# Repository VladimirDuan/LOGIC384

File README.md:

# LOGIC384
384LUTs ARM Cortex-M3&amp;FPGA development board.

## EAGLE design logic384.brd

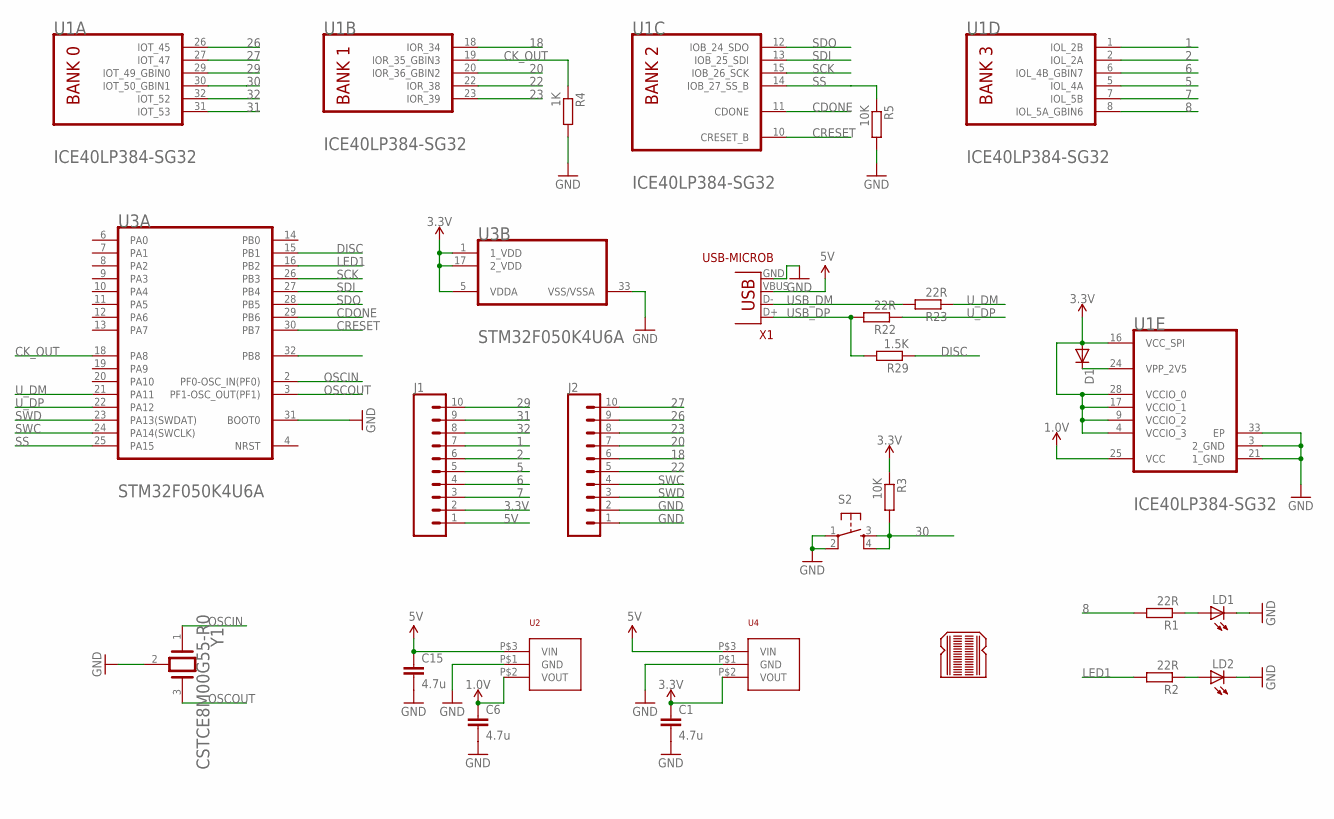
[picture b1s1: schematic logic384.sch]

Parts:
C1, C6, C15: 4.7u; 0402-CAP
D1: DIODE-SOD523; SOD523
J1, J2: CONN_10NO_SILK_PTH_FEMALE; 1X10_NO_SILK
LD1, LD2: LED0603; LED-0603
LOGO1: BREADBOARD_PATTERN; BREADBOARD_SPACING
R1, R2, R22, R23: 22R; R0402
R3, R5: 10K; R0402
R4: 1K; R0402
R29: 1.5K; R0402
S2: TAC_SWITCHSMD; TACTILE_SWITCH_SMD
U1: LATTICE_SEMICONDUCTOR_ICE40LP384-SG32LATTICE_SEMI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; LATTICE_SEMICONDUCTOR_ICE40LP384-SG32_1
U2, U4: MCP1703SOT-3.3V; SOT-23A
U3: STMICROELECTRONICS_STM32F050K4U6ASTMICROELECTRONI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; STMICROELECTRONICS_STM32F050K4U6A_1
X1: USB-MICROB
Y1: MURATA_CSTCE8M00G55-R0MURATA_CSTCE8M00G55-R0_0_0; MURATA_CSTCE8M00G55-R0_0

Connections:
1: J1.7, U1.1 (IOL_2B)
1.0V: C6.1, U1.25 (VCC), U2.P$2 (VOUT)
2: J1.6, U1.2 (IOL_2A)
3.3V: C1.1, D1.A, J1.2, R3.1, U1.4 (VCCIO_3), U1.9 (VCCIO_2), U1.16 (VCC_SPI), U1.17 (VCCIO_1), U1.28 (VCCIO_0), U3.1 (1_VDD), U3.5 (VDDA), U3.17 (2_VDD), U4.P$2 (VOUT)
5: J1.5, U1.5 (IOL_4A)
5V: C15.1, J1.1, U2.P$3 (VIN), U4.P$3 (VIN), X1.VBUS
6: J1.4, U1.6 (IOL_4B_GBIN7)
7: J1.3, U1.7 (IOL_5B)
8: R1.2, U1.8 (IOL_5A_GBIN6)
18: J2.6, U1.18 (IOR_34)
20: J2.7, U1.20 (IOR_36_GBIN2)
22: J2.5, U1.22 (IOR_38)
23: J2.8, U1.23 (IOR_39)
26: J2.9, U1.26 (IOT_45)
27: J2.10, U1.27 (IOT_47)
29: J1.10, U1.29 (IOT_49_GBIN0)
30: R3.2, S2.3, S2.4, U1.30 (IOT_50_GBIN1)
31: J1.9, U1.31 (IOT_53)
32: J1.8, U1.32 (IOT_52)
CDONE: U1.11 (CDONE), U3.29 (PB6)
CK_OUT: R4.1, U1.19 (IOR_35_GBIN3), U3.18 (PA8)
CRESET: U1.10 (CRESET_B), U3.30 (PB7)
DISC: R29.1, U3.15 (PB1)
GND: C1.2, C6.2, C15.2, J2.1, J2.2, LD1.C, LD2.C, R4.2, R5.2, S2.1, S2.2, U1.3 (2_GND), U1.21 (1_GND), U1.33 (EP), U2.P$1 (GND), U3.31 (BOOT0), U3.33 (VSS/VSSA), U4.P$1 (GND), X1.GND, Y1.2
LED1: R2.2, U3.16 (PB2)
unnamed: LD1.A, R1.1
unnamed: LD2.A, R2.1
unnamed: D1.C, U1.24 (VPP_2V5)
OSCIN: U3.2 (PF0-OSC_IN(PF0)), Y1.1
OSCOUT: U3.3 (PF1-OSC_OUT(PF1)), Y1.3
SCK: U1.15 (IOB_26_SCK), U3.26 (PB3)
SDI: U1.13 (IOB_25_SDI), U3.27 (PB4)
SDO: U1.12 (IOB_24_SDO), U3.28 (PB5)
SS: R5.1, U1.14 (IOB_27_SS_B), U3.25 (PA15)
SWC: J2.4, U3.24 (PA14(SWCLK))
SWD: J2.3, U3.23 (PA13(SWDAT))
USB_DM: R23.2, X1.D-
USB_DP: R22.2, R29.2, X1.D+
U_DM: R23.1, U3.21 (PA11)
U_DP: R22.1, U3.22 (PA12)

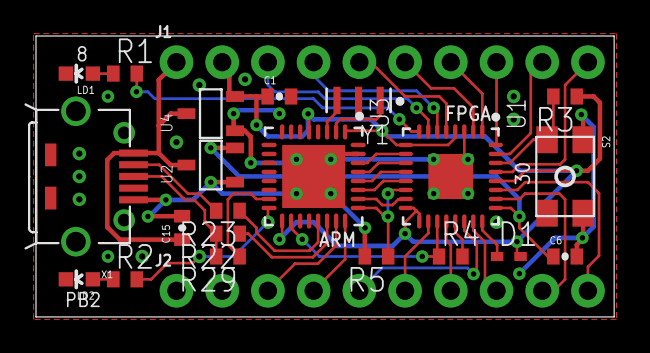
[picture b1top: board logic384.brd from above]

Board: 2 copper layers, 32.1 x 15.6 mm, 24 parts (0 on the bottom side), 40 nets.

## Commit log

2019-01-15 Upload design files.

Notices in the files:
parts and their libraries:
SparkFun-Aesthetics: Licensing: Creative Commons ShareAlike 4.0 International - https://creativecommons.org/licenses/by-sa/4.0
